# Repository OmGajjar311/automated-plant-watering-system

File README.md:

# automated-plant-watering-system
ESP32-based automated plant-watering system with capacitive soil-moisture sensing and custom KiCad PCB.

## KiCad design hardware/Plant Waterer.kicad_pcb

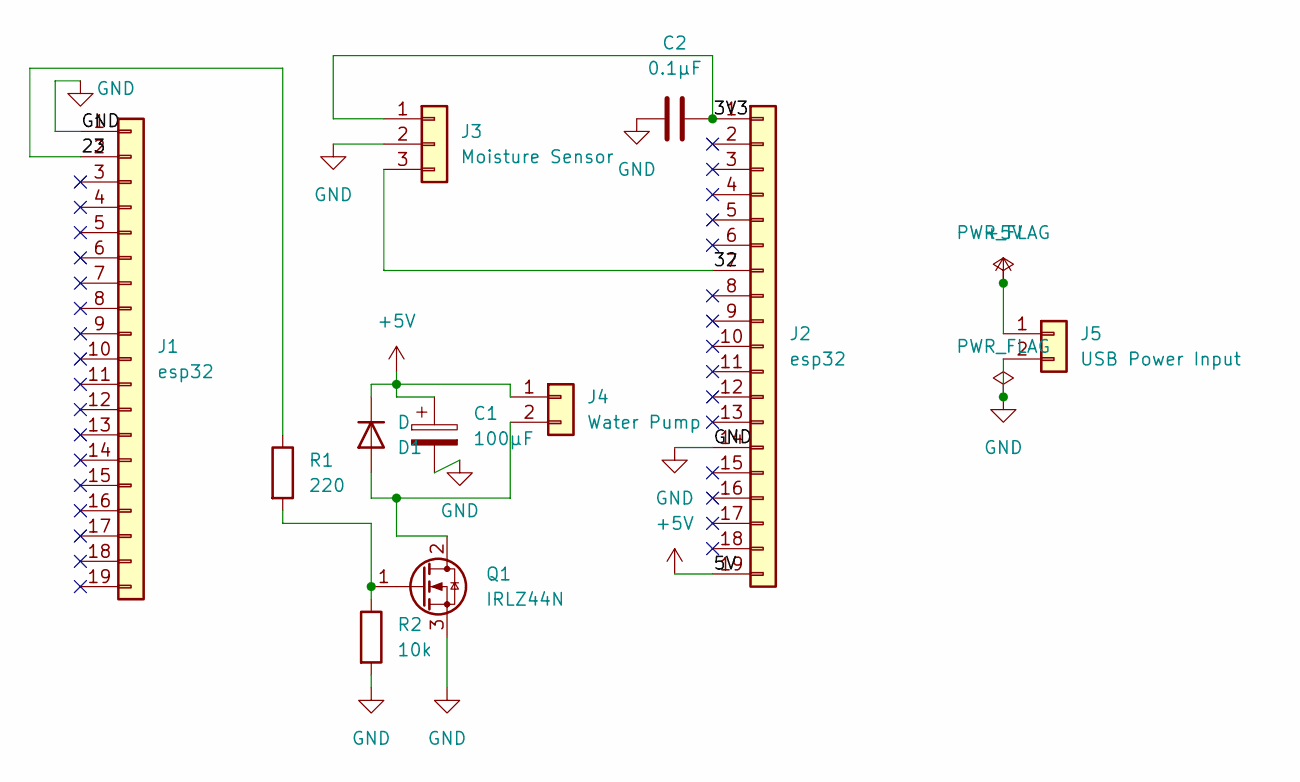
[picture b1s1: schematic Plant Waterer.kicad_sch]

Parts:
C1: 100µF; CP_Radial_D5.0mm_P2.00mm
C2: 0.1µF; C_Disc_D5.0mm_W2.5mm_P5.00mm
D1: D; D_DO-35_SOD27_P7.62mm_Horizontal
J1, J2: esp32; PinHeader_1x19_P2.54mm_Vertical
J3: Moisture Sensor; PinHeader_1x03_P2.54mm_Vertical
J4: Water Pump; Altech_AK300_1x02_P5.00mm_45-Degree
J5: USB Power Input; Altech_AK300_1x02_P5.00mm_45-Degree
Q1: IRLZ44N; TO-220-3_Vertical
R1: 220; R_Axial_DIN0207_L6.3mm_D2.5mm_P10.16mm_Horizontal
R2: 10k; R_Axial_DIN0207_L6.3mm_D2.5mm_P10.16mm_Horizontal

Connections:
+5V: C1.1, D1.1 (K), J2.19, J4.1, J5.1
/3V3: C2.1, J2.1, J3.1 (VCC)
/23: J1.2, R1.1
/32: J2.7, J3.3
GND: C1.2, C2.2, J1.1, J2.14, J3.2, J5.2, Q1.3 (S), R2.2
unnamed: D1.2 (A), J4.2, Q1.2 (Drain)
unnamed: Q1.1 (G), R1.2, R2.1

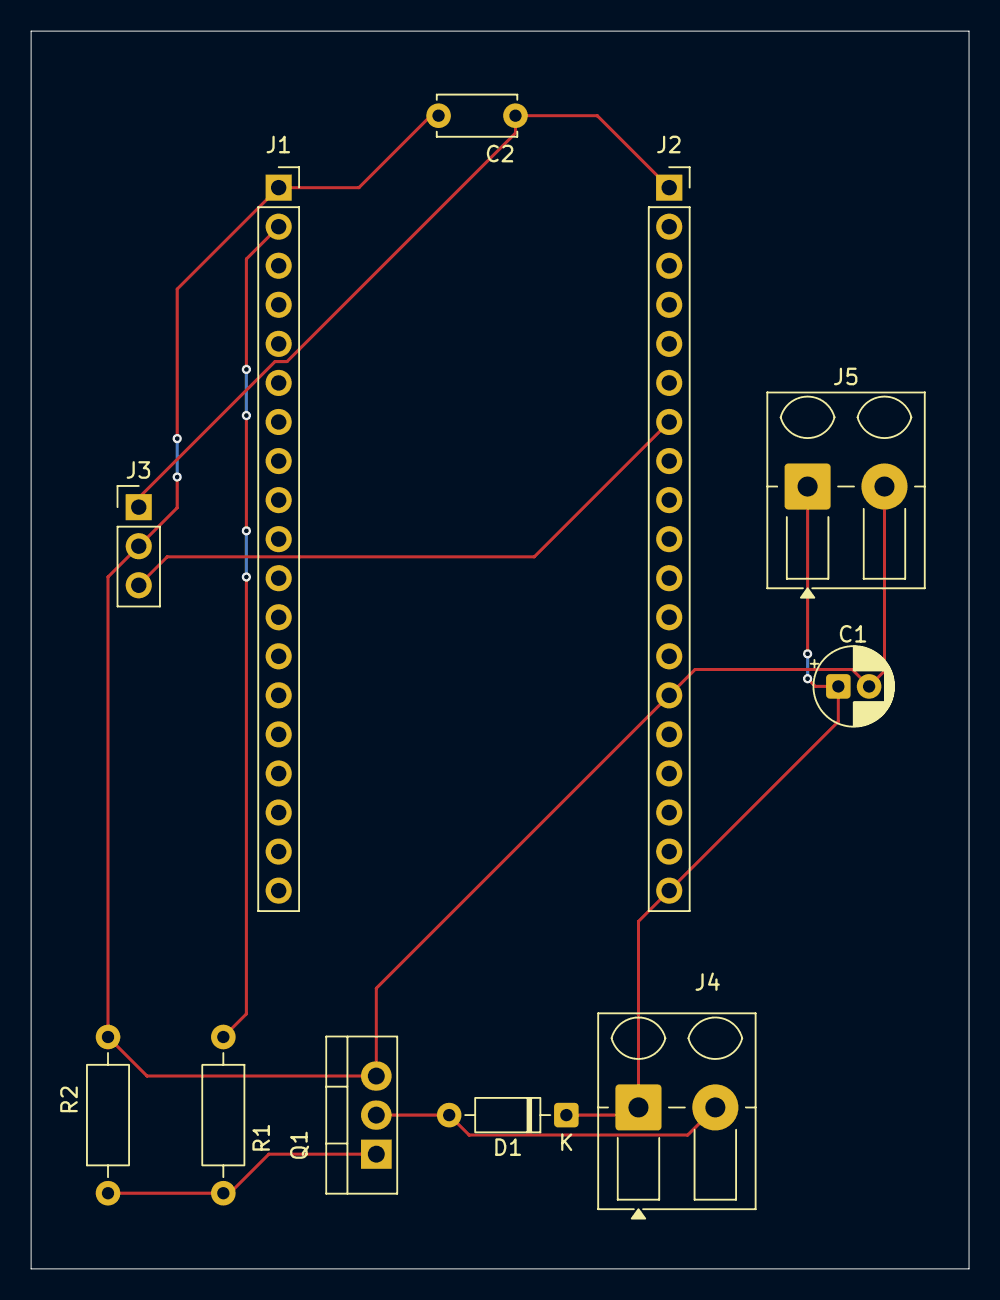
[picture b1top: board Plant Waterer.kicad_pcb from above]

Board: 2 copper layers, 61.0 x 80.5 mm, 11 parts (0 on the bottom side), 7 nets.
